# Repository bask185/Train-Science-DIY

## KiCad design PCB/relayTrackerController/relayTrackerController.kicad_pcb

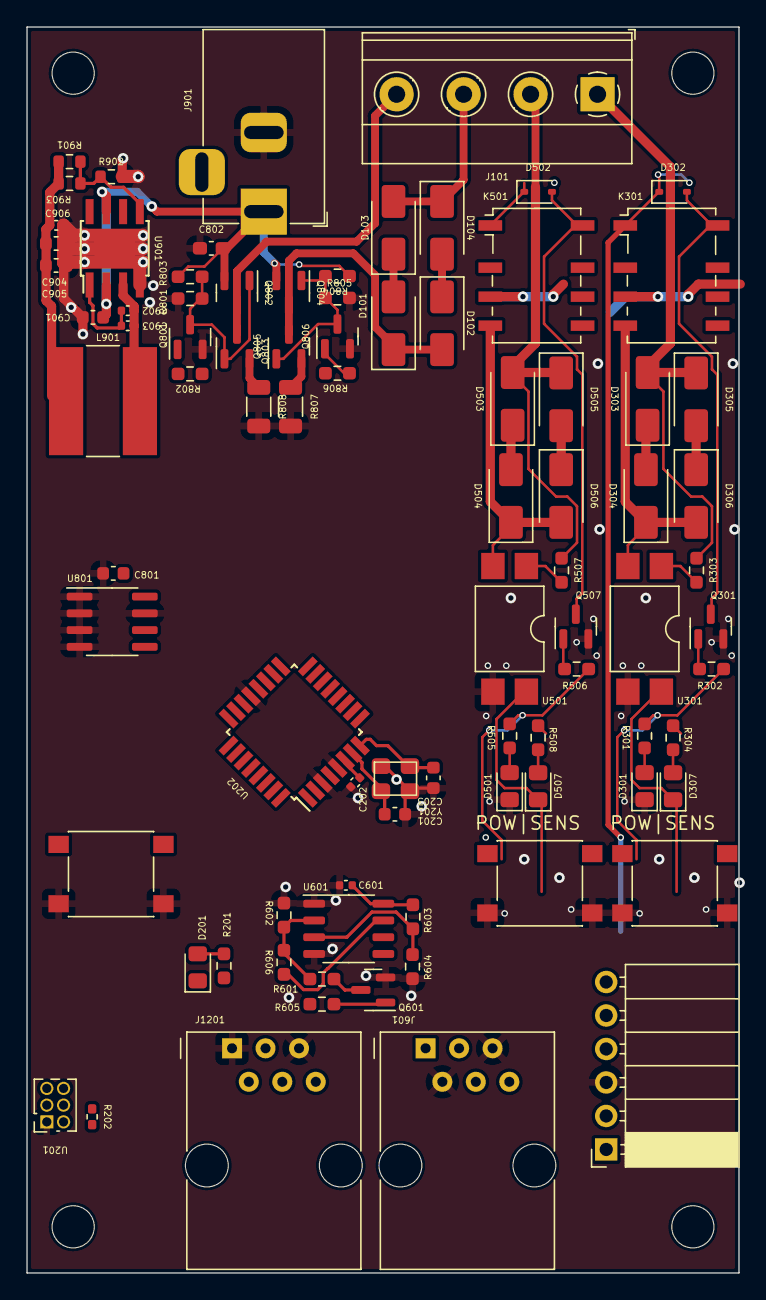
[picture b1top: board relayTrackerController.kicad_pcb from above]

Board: 2 copper layers, 54.0 x 94.5 mm, 86 parts (0 on the bottom side), 61 nets.

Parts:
C201, C203: 12pF; C_0603_1608Metric
C202, C601, C902, C906: 100nF; C_0402_1005Metric
C801: 100nF; C_0603_1608Metric
C802: 100nF; C_0603_1608Metric_Pad1.08x0.95mm_HandSolder
C901, C904, C905: 22uF; C_0603_1608Metric
C903: 22nF; C_0402_1005Metric
D101, D102, D103, D104, D303, D304, D305, D306, D503, D504, D505, D506: SS53; D_SMA
D201, D301, D307, D501, D507: LED; LED_0805_2012Metric_Pad1.15x1.40mm_HandSolder
D302, D502: 1N4148WS; D_SOD-323
J101: Screw_Terminal_01x04; TerminalBlock_Phoenix_MKDS-1,5-4-5.08_1x04_P5.08mm_Horizont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
J403: Conn_01x06_Socket; PinSocket_1x06_P2.54mm_Horizontal
J601, J1201: RJ12
J901: Jack-DC; BarrelJack_Horizontal
K301, K501: G6K-2F-Y-TR DC12; Relay_DPDT_Omron_G6K-2F-Y
L901: L; L_Bourns-SRN8040_8x8.15mm
Q301, Q507, Q601, Q801, Q806: NPN_TOR; SOT-23
Q802, Q804: P-channel; SOT-23
Q803, Q805: N-channel; SOT-23
R201: 6k2; R_0603_1608Metric_Pad0.98x0.95mm_HandSolder
R202: 10k; R_0402_1005Metric_Pad0.72x0.64mm_HandSolder
R301, R304, R505, R508: 3k3; R_0603_smalltext
R302, R506, R605, R802, R806: 1k; R_0603_smalltext
R303, R507: 47R; R_0603_smalltext
R601: 47k; R_0603_smalltext
R602: 150k; R_0603_smalltext
R603, R803, R804: 10k; R_0603_smalltext
R604: 22k; R_0603_smalltext
R606: 220k; R_0603_smalltext
R801, R805: 15k; R_0603_smalltext
R807, R808: 0R1; R_1206_3216Metric
R901: 220k; R_0603_1608Metric
R902: 20k; R_0603_1608Metric
R903: 150k; R_0603_1608Metric
SW201, SW301, SW501: SW_Push; tactile_SMD_6mm
U201: HEADER_3x2; PinSocket_2x03_P1.27mm_Vertical
U202: ATmega328-A; TQFP-32_7x7mm_P0.8mm
U301, U501: EL814; SMDIP-4_W9.53mm
U601: LM311; SOP-8_3.9x4.9mm_P1.27mm
U801: 24LC256; SOIC-8_3.9x4.9mm_P1.27mm
U901: MT2499A; TI_SO-PowerPAD-8
Y201: Crystal_GND2; crystal_arduino

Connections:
+5V: C202.1, C601.1, C801.2, C904.1, C905.1, C906.1, J403.5, J1201.6, L901.2, R201.1, R202.1, R304.1, R508.1, R603.1, R901.1, R903.2, U201.5, U202.4 (VCC), U202.6 (VCC), U202.18 (AVCC), U601.8 (V+), U801.8 (VCC)
/B2B/Rx: J403.1, U202.31 (PD1)
/B2B/Tx: J403.2, U202.30 (PD0)
/CPU/A: R802.1, U202.14 (PB2)
/CPU/B: R806.2, U201.3, U202.15 (PB3)
/CPU/CS: Q803.2 (S), Q805.2 (S), R807.1, R808.1, U202.23 (PC0)
/CPU/LED: D201.1 (K), U201.4, U202.17 (PB5)
/CPU/Lnet.Rx: R606.2, U202.12 (PB0), U601.7
/CPU/Lnet.Tx: R605.2, U202.13 (PB1)
/CPU/MISO: SW201.1, U201.6, U202.16 (PB4)
/CPU/SCL: U202.28 (PC5), U801.6 (SCL)
/CPU/SDA: U202.27 (PC4), U801.5 (SDA)
/CPU/X1: C201.2, U202.7 (XTAL1/PB6), Y201.1
/CPU/X2: C203.2, U202.8 (XTAL2/PB7), Y201.3
/CPU/brake: J1201.3, U202.25 (PC2)
/CPU/dir: J1201.4, U202.24 (PC1)
/CPU/relay1.add: SW301.1, U202.2 (PD4)
/CPU/relay1.relay: R301.1, R302.1, U202.1 (PD3)
/CPU/relay1.sensor: D307.1 (K), U202.32 (PD2), U301.4
/CPU/relay2.add: SW501.1, U202.11 (PD7)
/CPU/relay2.relay: R505.1, R506.1, U202.10 (PD6)
/CPU/relay2.sensor: D507.1 (K), U202.9 (PD5), U501.4
/CPU/reset: R202.2, U201.2, U202.29 (~RESET/PC6)
/CPU/throttle: J1201.2, U202.26 (PC3)
/PWM/OUT_A: J101.4, Q802.3 (D), Q803.3 (D)
/PWM/OUT_B: D101.1 (K), D102.2 (A), J403.6, K301.3, K501.3, Q804.3 (D), Q805.3 (D)
/relay1/TRACK: D303.2 (A), D305.1 (K), J101.1, R303.1
/relay2/TRACK: D503.2 (A), D505.1 (K), J101.2, R507.1
GND: C201.1, C202.2, C203.1, C601.2, C801.1, C802.1, C901.2, C904.2, C905.2, C906.2, D301.1 (K), D501.1 (K), J403.3, J601.2, J601.5, J901.2, J1201.1, J1201.5, Q301.2 (E), Q507.2 (E), Q601.2 (E), Q801.2 (E), Q806.2 (E), R602.2, R604.1, R801.1, R805.2, R807.2, R808.2, R902.2, SW201.2, SW301.2, SW501.2, U201.1, U202.3 (GND), U202.5 (GND), U202.21 (GND), U301.3, U501.3, U601.1 (GND), U601.4 (V-), U801.1 (A0), U801.2 (A1), U801.3 (A2), U801.4 (GND), U801.7 (WP), U901.4 (GND), U901.9 (GND), Y201.2 (GND), Y201.4 (GND)
unnamed: D101.2 (A), D103.1 (K)
unnamed: D102.1 (K), D104.2 (A)
unnamed: D103.2 (A), D104.1 (K), J101.3
unnamed: D201.2 (A), R201.2
unnamed: D301.2 (A), R301.2
unnamed: D302.2 (A), K301.8, Q301.3 (C)
unnamed: D303.1 (K), D304.2 (A)
unnamed: D304.1 (K), D306.2 (A), K301.4, U301.2
unnamed: D305.2 (A), D306.1 (K)
unnamed: D307.2 (A), R304.2
unnamed: D501.2 (A), R505.2
unnamed: D502.2 (A), K501.8, Q507.3 (C)
unnamed: D503.1 (K), D504.2 (A)
unnamed: D504.1 (K), D506.2 (A), K501.4, U501.2
unnamed: D505.2 (A), D506.1 (K)
unnamed: D507.2 (A), R508.2
unnamed: Q301.1 (B), R302.2
unnamed: Q507.1 (B), R506.2
unnamed: Q601.1 (B), R605.1
unnamed: J601.3, J601.4, Q601.3 (C), R601.1
unnamed: Q801.1 (B), R802.2
unnamed: Q801.3 (C), Q802.1 (G), Q803.1 (G), R801.2, R803.2
unnamed: Q804.1 (G), Q805.1 (G), Q806.3 (C), R804.2, R805.1
unnamed: Q806.1 (B), R806.1
unnamed: R303.2, U301.1
unnamed: R507.2, U501.1
unnamed: R601.2, R602.1, R606.1, U601.2 (+)
unnamed: R603.2, R604.2, U601.3 (-)
unnamed: C902.1, C903.1, U901.1 (BS)
unnamed: R901.2, R902.1, R903.1, U901.5 (FB)
unnamed: C902.2, C903.2, L901.1, U901.3 (SW)
VCC: C802.2, C901.1, D302.1 (K), D502.1 (K), J403.4, J601.1, J601.6, J901.1, K301.1, K501.1, Q802.2 (S), Q804.2 (S), R803.1, R804.1, U901.2 (Vin), U901.7 (EN)

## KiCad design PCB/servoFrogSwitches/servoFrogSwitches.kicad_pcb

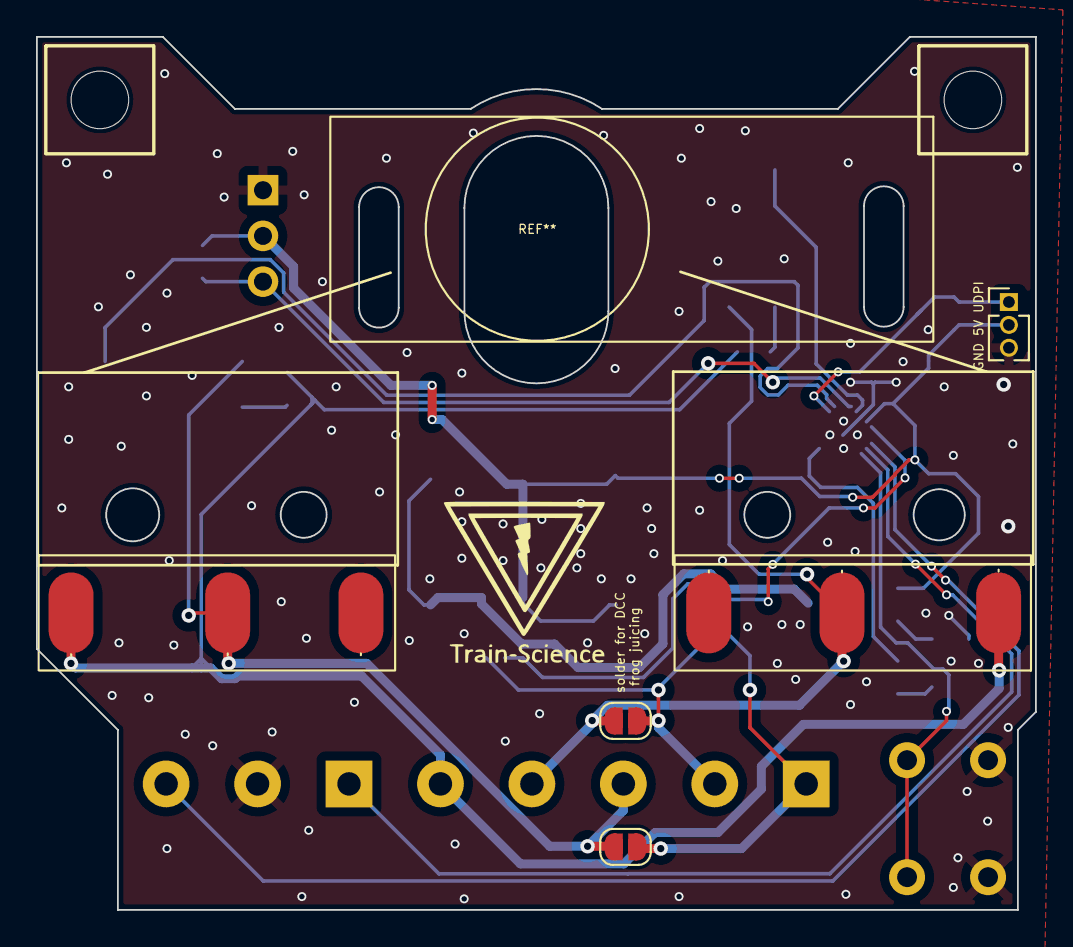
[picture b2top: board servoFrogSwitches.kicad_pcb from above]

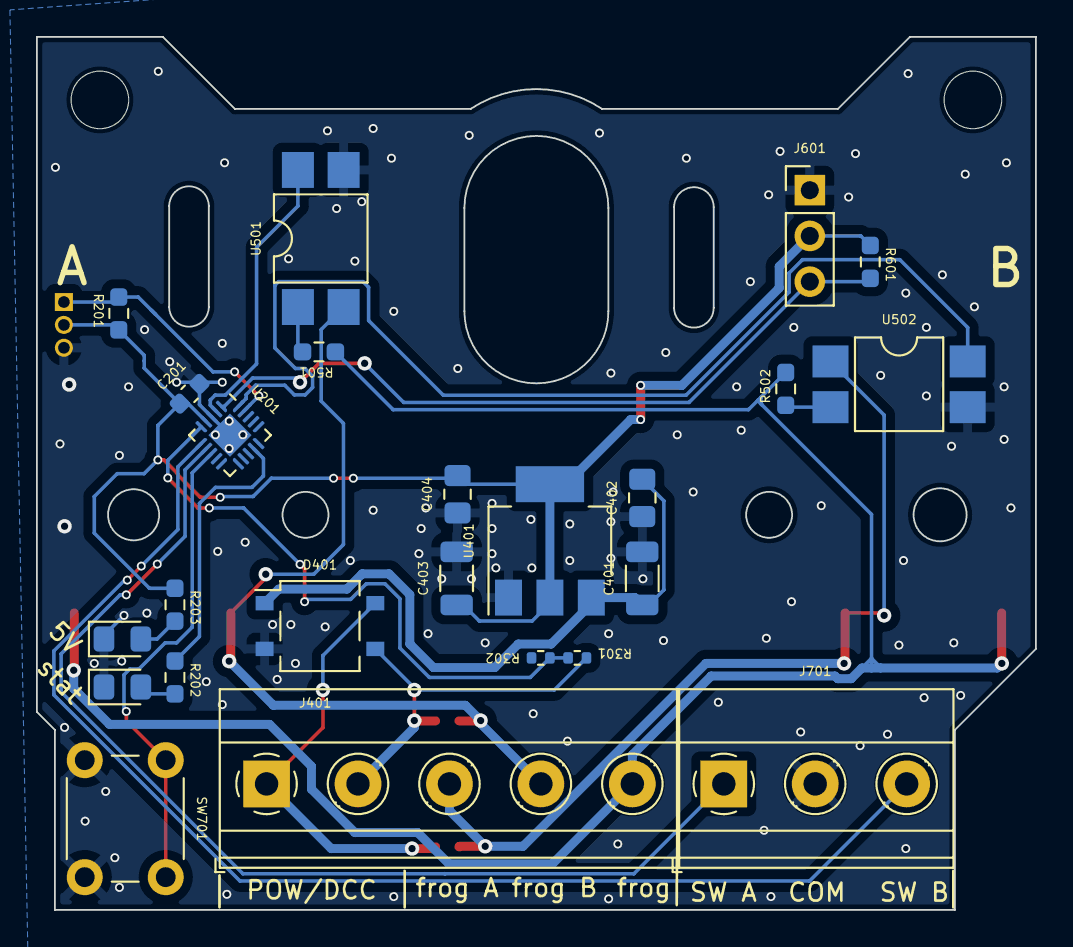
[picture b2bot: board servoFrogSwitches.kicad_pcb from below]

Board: 2 copper layers, 55.5 x 48.5 mm, 29 parts (24 on the bottom side), 21 nets.

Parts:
C201: 100nF; C_0603_1608Metric
C401: 47uF; C_1206_3216Metric
C402, C404: 100nF; C_0805_2012Metric_Pad1.18x1.45mm_HandSolder
C403: 100uF; C_1206_3216Metric
D201, D202: LED; LED_0805_2012Metric_Pad1.15x1.40mm_HandSolder
D401: MB10S; TO-269AA
J201: Conn_01x03_Pin; PinHeader_1x03_P1.27mm_Vertical
J401: Screw_Terminal_01x05; TerminalBlock_Phoenix_MKDS-1,5-5-5.08_1x05_P5.08mm_Horizont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
J601: Conn_01x03; PinHeader_1x03_P2.54mm_Vertical
J701: Screw_Terminal_01x03; TerminalBlock_Phoenix_MKDS-1,5-3-5.08_1x03_P5.08mm_Horizont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
JP401, JP402: SolderJumper_2_Open; SolderJumper-2_P1.3mm_Open_RoundedPad1.0x1.5mm
R201, R601: 10k; R_0603_smalltext
R202, R203: 680R; R_0603_smalltext
R301: 26k; R_0402_1005Metric
R302: 10k; R_0402_1005Metric
R501, R502: 1k5; R_0603_smalltext
SW501, SW502: SW_SPDT; microswitch
SW701: 6mm_tactile; SW_PUSH_6mm
U201: ATtiny1616-M; VQFN-20-1EP_3x3mm_P0.4mm_EP1.7x1.7mm
U401: AMS1117-5.0; SOT-223-3_TabPin2
U501, U502: EL814; SMDIP-4_W7.62mm

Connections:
+5V: C201.1, C403.1, C404.2, J201.2, J601.2, R201.1, R203.1, R601.1, U201.4 (VCC), U401.2 (VO)
/DCC/DCC_A: D401.3, J401.2, JP401.2 (B), R301.1
/DCC/DCC_TTL: R301.2, R302.1, U201.5 (PA4)
/attiny/LIM_A: U201.20 (PA1), U502.4
/attiny/LIM_B: U201.2 (PA3), U501.4
/attiny/UPDI: J201.1, R201.2, U201.19 (~RESET/PA0)
/attiny/control_A: J701.3, U201.6 (PA5)
/attiny/control_B: J701.1, U201.7 (PA6)
/attiny/finetune: SW701.1 (A), U201.8 (PA7)
/attiny/servo: J601.3, R601.2, U201.1 (PA2)
/limitSwitches/DCC_A: J401.4, JP401.1 (A), SW501.3 (C), U501.2
/limitSwitches/DCC_B: J401.3, JP402.1 (A), SW502.3 (C), U502.1
/limitSwitches/FROG: J401.5, R501.1, R502.2, SW501.2 (B), SW502.2 (B)
/power/DCC_B: D401.4, J401.1, JP402.2 (B)
GND: C201.2, C401.2, C402.1, C403.2, C404.1, D201.1 (K), D202.1 (K), D401.2 (-), J201.3, J601.1, J701.2, SW701.2 (B), U201.3 (GND), U201.21 (GND), U401.1 (GND), U501.3, U502.3
unnamed: D201.2 (A), R202.2
unnamed: D202.2 (A), R203.2
unnamed: R501.2, U501.1
unnamed: R502.1, U502.2
unnamed: R202.1, U201.14 (PB0)
VCC: C401.1, C402.2, D401.1 (+), U401.3 (VI)

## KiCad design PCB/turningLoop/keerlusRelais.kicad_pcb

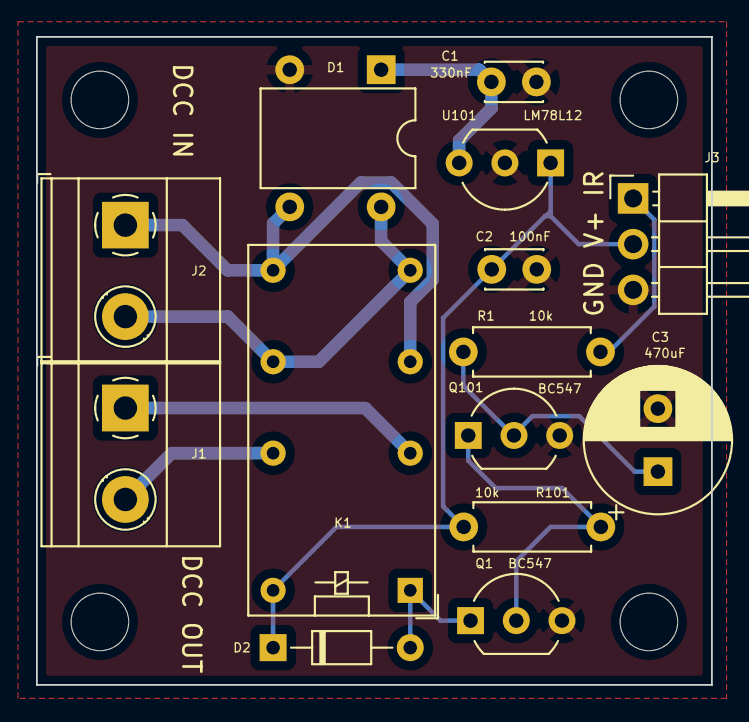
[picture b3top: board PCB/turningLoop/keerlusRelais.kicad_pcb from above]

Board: 2 copper layers, 37.5 x 36.0 mm, 14 parts (0 on the bottom side), 11 nets.

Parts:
C1: 330nF; C_Disc_D3.0mm_W2.0mm_P2.50mm
C2: 100nF; C_Disc_D3.0mm_W2.0mm_P2.50mm
C3: 470uF; CP_Radial_D8.0mm_P3.50mm
D1: D_Bridge_+-AA; Diode_Bridge_DIP-4_W7.62mm_P5.08mm
D2: D; D_DO-34_SOD68_P7.62mm_Horizontal
J1: DCC_out; TerminalBlock_Phoenix_MKDS-1,5-2-5.08_1x02_P5.08mm_Horizont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
J2: DCC_IN; TerminalBlock_Phoenix_MKDS-1,5-2-5.08_1x02_P5.08mm_Horizont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
J3: Conn_01x03_Male; PinHeader_1x03_P2.54mm_Horizontal
K1: G5V-2; Relay_DPDT_Omron_G5V-2
Q1, Q101: BC547; TO-92_Inline_Wide
R1, R101: 10k; R_Axial_DIN0207_L6.3mm_D2.5mm_P7.62mm_Horizontal
U101: LM78L12; TO-92_Inline_Wide

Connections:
+12V: C2.1, D2.1 (K), J3.2, K1.16, R101.2, U101.1 (VO)
/DCC_A_IN: D1.3, J2.1, K1.6, K1.9
/DCC_A_OUT: J1.1, K1.4
/DCC_B_IN: D1.4, J2.2, K1.8, K1.11
/DCC_B_OUT: J1.2, K1.13
GND: C1.2, C2.2, C3.2, D1.2 (-), J3.3, Q1.3 (E), Q101.3 (E), U101.2 (GND)
unnamed: D2.2 (A), K1.1, Q1.1 (C)
unnamed: J3.1, R1.2
unnamed: Q1.2 (B), Q101.1 (C), R101.1
unnamed: C3.1, Q101.2 (B), R1.1
VCC: C1.1, D1.1 (+), U101.3 (VI)

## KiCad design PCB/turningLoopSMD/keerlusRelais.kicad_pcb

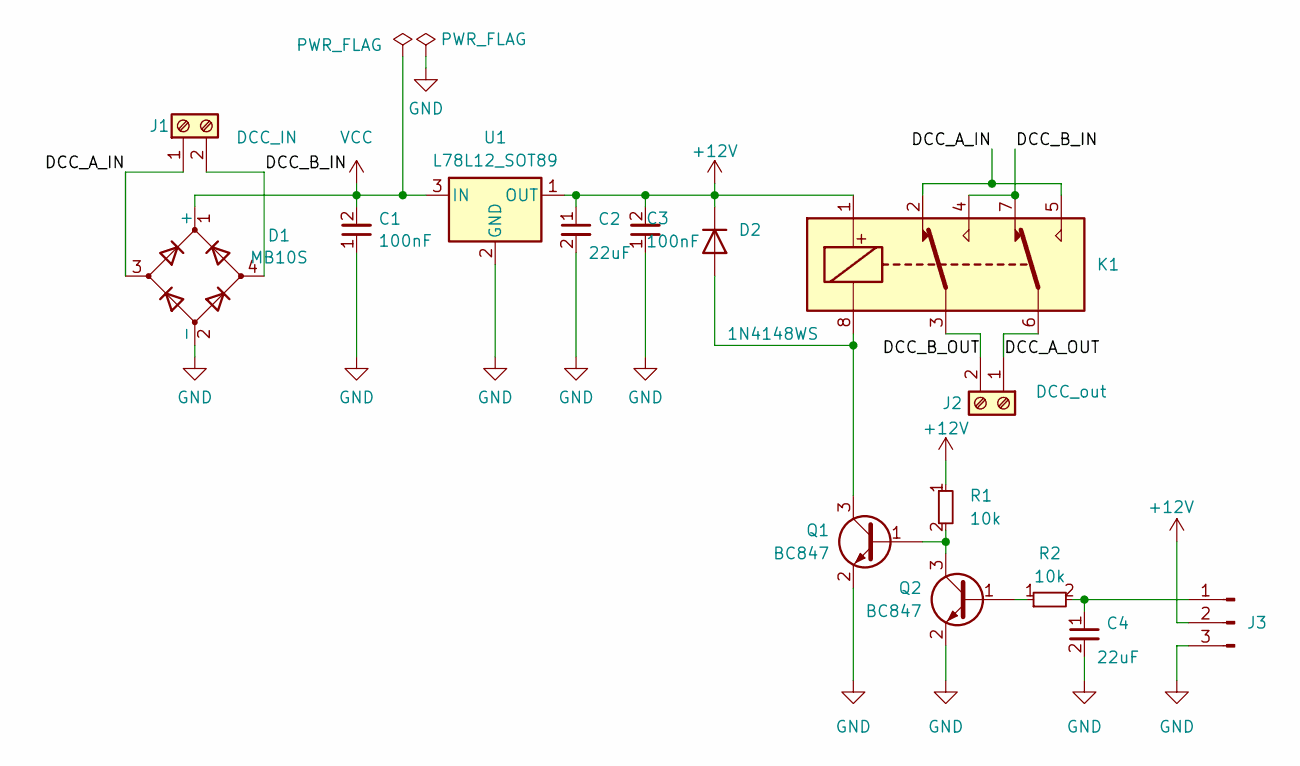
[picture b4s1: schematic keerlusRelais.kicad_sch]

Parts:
C1, C3: 100nF; C_0603_1608Metric; JLCPCB Part# C14663
C2, C4: 22uF; C_1206_3216Metric; JLCPCB Part# C12891
D1: MB10S; MB10s; JLCPCB Part# C2488
D2: 1N4148WS; D_SOD-323; JLCPCB Part# C2128
J1: DCC_IN; TerminalBlock_Phoenix_MKDS-1,5-2-5.08_1x02_P5.08mm_Horizont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
J2: DCC_out; TerminalBlock_Phoenix_MKDS-1,5-2-5.08_1x02_P5.08mm_Horizont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
J3: Conn_01x03_Male; PinHeader_1x03_P2.54mm_Horizontal
K1: G6K-2F-Y-TR DC5; Relay_DPDT_Omron_G6K-2F-Y; JLCPCB Part# C397192
Q1, Q2: BC847; SOT-23; JLCPCB Part# C181140
R1, R2: 10k; R_0603_smalltext; JLCPCB Part# C25804
U1: L78L12_SOT89; SOT-89-3; JLCPCB Part# C75501

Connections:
+12V: C2.1, C3.2, D2.1 (K), J3.2, K1.1, R1.1, U1.1 (OUT)
/DCC_A_IN: D1.3, J1.1, K1.2, K1.5
/DCC_A_OUT: J2.1, K1.6
/DCC_B_IN: D1.4, J1.2, K1.4, K1.7
/DCC_B_OUT: J2.2, K1.3
GND: C1.1, C2.2, C3.1, C4.2, D1.2 (-), J3.3, Q1.2 (E), Q2.2 (E), U1.2 (GND)
unnamed: D2.2 (A), K1.8, Q1.3 (C)
unnamed: C4.1, J3.1, R2.2
unnamed: Q1.1 (B), Q2.3 (C), R1.2
unnamed: Q2.1 (B), R2.1
VCC: C1.2, D1.1 (+), U1.3 (IN)

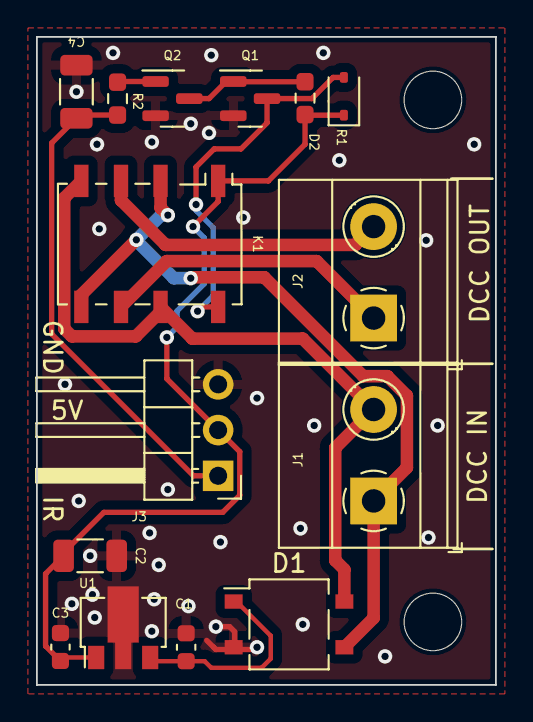
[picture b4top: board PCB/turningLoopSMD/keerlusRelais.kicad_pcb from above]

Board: 2 copper layers, 25.5 x 36.0 mm, 15 parts (0 on the bottom side), 11 nets.

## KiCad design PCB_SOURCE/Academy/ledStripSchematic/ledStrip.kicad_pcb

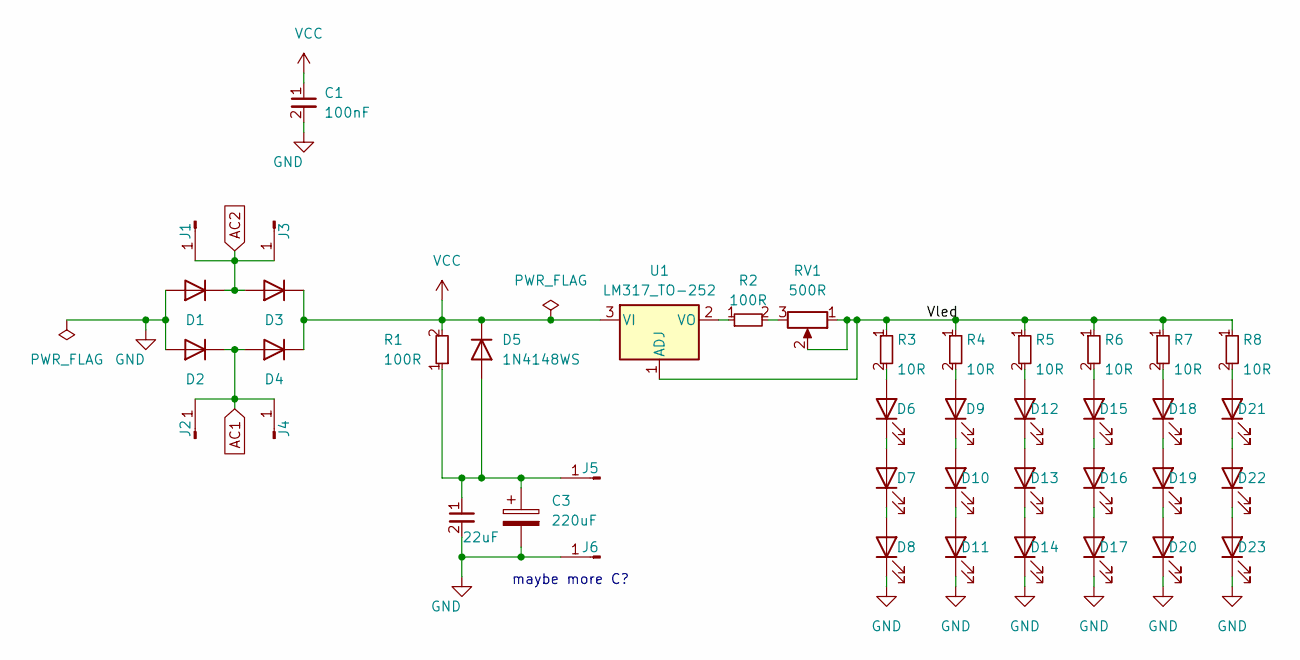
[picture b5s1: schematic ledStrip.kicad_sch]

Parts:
C1: 100nF; C_0603_1608Metric; JLCPCB Part# C14663
C2: 22uF; C_1206_3216Metric; JLCPCB Part# C12891
C3: 220uF; C_Elec_8x10.2; JLCPCB Part# C136294
D1, D2, D3, D4, D5: 1N4148WS; D_SOD-323; JLCPCB Part# C2128
D6, D7, D8, D9, D10, D11, D12, D13, D14, D15, D16, D17, D18, D19, D20, D21, D22, D23: LED; LED_0805_2012Metric; JLCPCB Part# C965820
J1, J2, J3, J4, J5, J6: Conn_01x01_Pin; 01_solderpad_2.54
R1: 100R; R_0805_handsolder-smalltext; JLCPCB Part# C17408
R2: 100R; R_0603_smalltext; JLCPCB Part# C22775
R3, R4, R5, R6, R7, R8: 10R; R_0603_smalltext; JLCPCB Part# C22859
RV1: 500R; Potentiometer_Bourns_TC33X_Vertical; JLCPCB Part# C720649
U1: LM317_TO-252; TO-252-2; JLCPCB Part# C75510

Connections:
/Vled: R3.1, R4.1, R5.1, R6.1, R7.1, R8.1, RV1.1, RV1.2, U1.1 (ADJ)
AC1: D2.1 (K), D4.2 (A), J2.1, J4.1
AC2: D1.1 (K), D3.2 (A), J1.1, J3.1
GND: C1.2, C2.2, C3.2, D1.2 (A), D2.2 (A), D8.1 (K), D11.1 (K), D14.1 (K), D17.1 (K), D20.1 (K), D23.1 (K), J6.1
unnamed: C2.1, C3.1, D5.2 (A), J5.1, R1.1
unnamed: D6.2 (A), R3.2
unnamed: D6.1 (K), D7.2 (A)
unnamed: D7.1 (K), D8.2 (A)
unnamed: D9.2 (A), R4.2
unnamed: D9.1 (K), D10.2 (A)
unnamed: D10.1 (K), D11.2 (A)
unnamed: D12.2 (A), R5.2
unnamed: D12.1 (K), D13.2 (A)
unnamed: D13.1 (K), D14.2 (A)
unnamed: D15.2 (A), R6.2
unnamed: D15.1 (K), D16.2 (A)
unnamed: D16.1 (K), D17.2 (A)
unnamed: D18.2 (A), R7.2
unnamed: D18.1 (K), D19.2 (A)
unnamed: D19.1 (K), D20.2 (A)
unnamed: D21.2 (A), R8.2
unnamed: D21.1 (K), D22.2 (A)
unnamed: D22.1 (K), D23.2 (A)
unnamed: R2.2, RV1.3
unnamed: R2.1, U1.2 (VO)
VCC: C1.1, D3.1 (K), D4.1 (K), D5.1 (K), R1.2, U1.3 (VI)

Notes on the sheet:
maybe more C?

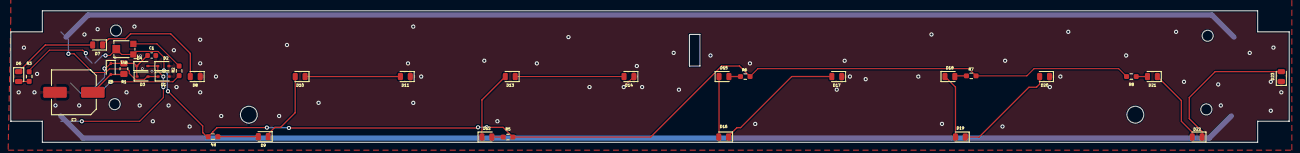
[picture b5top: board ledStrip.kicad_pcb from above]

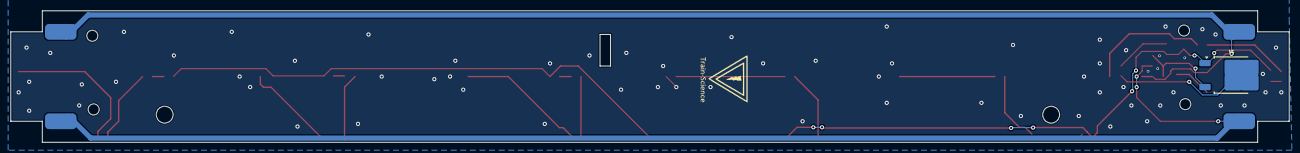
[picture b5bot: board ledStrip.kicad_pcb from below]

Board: 2 copper layers, 243.0 x 25.0 mm, 39 parts (5 on the bottom side), 26 nets.

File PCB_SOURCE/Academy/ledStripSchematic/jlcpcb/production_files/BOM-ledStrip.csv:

Comment,Designator,Footprint,LCSC
220uF,C3,C_Elec_8x10.2,C136294
100nF,C1,C_0603_1608Metric,C14663
100R,R1,R_0805_handsolder-smalltext,C17408
1N4148WS,"D1,D2,D3,D4,D5",D_SOD-323,C2128
100R,R2,R_0603_smalltext,C22775
10R,"R3,R4,R5,R6,R7,R8",R_0603_smalltext,C22859
500R,RV1,Potentiometer_Bourns_TC33X_Vertical,C720649
LED,"D10,D11,D12,D13,D14,D15,D16,D17,D18,D19,D20,D21,D22,D23,D6,D7,D8,D9",LED_0805_2012Metric,C965820

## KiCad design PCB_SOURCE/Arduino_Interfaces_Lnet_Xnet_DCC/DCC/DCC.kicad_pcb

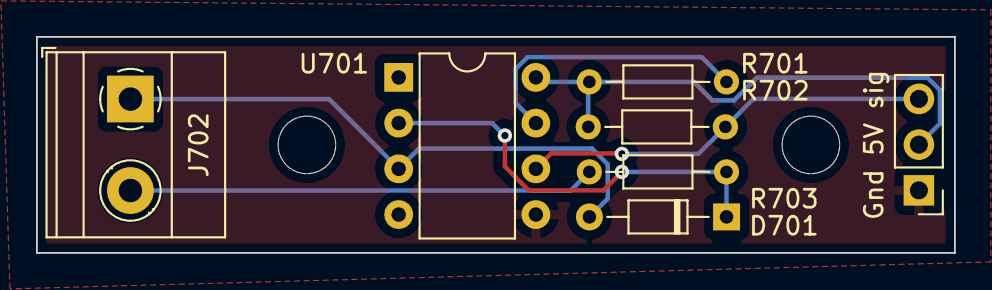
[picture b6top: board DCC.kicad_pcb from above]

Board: 2 copper layers, 51.0 x 12.0 mm, 7 parts (0 on the bottom side), 7 nets.

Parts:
D701: D; D_DO-34_SOD68_P7.62mm_Horizontal
J701: Conn_01x03_Male; PinHeader_1x03_P2.54mm_Vertical
J702: Screw_Terminal_01x02; TerminalBlock_Phoenix_MKDS-1,5-2-5.08_1x02_P5.08mm_Horizont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
R701, R702: 10k; R_Axial_DIN0204_L3.6mm_D1.6mm_P7.62mm_Horizontal
R703: 1k; R_Axial_DIN0204_L3.6mm_D1.6mm_P7.62mm_Horizontal
U701: 6N137; DIP-8_W7.62mm

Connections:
+5V: J701.2, R701.1, R702.1, U701.8 (VCC)
DCC-A: J702.2, R703.1
DCC-B: D701.2 (A), J702.1, U701.3 (C)
DCC_IN: J701.3, R702.2, U701.6 (VO)
GND: J701.1, U701.5 (GND)
unnamed: D701.1 (K), R703.2, U701.2 (A)
unnamed: R701.2, U701.7 (EN)

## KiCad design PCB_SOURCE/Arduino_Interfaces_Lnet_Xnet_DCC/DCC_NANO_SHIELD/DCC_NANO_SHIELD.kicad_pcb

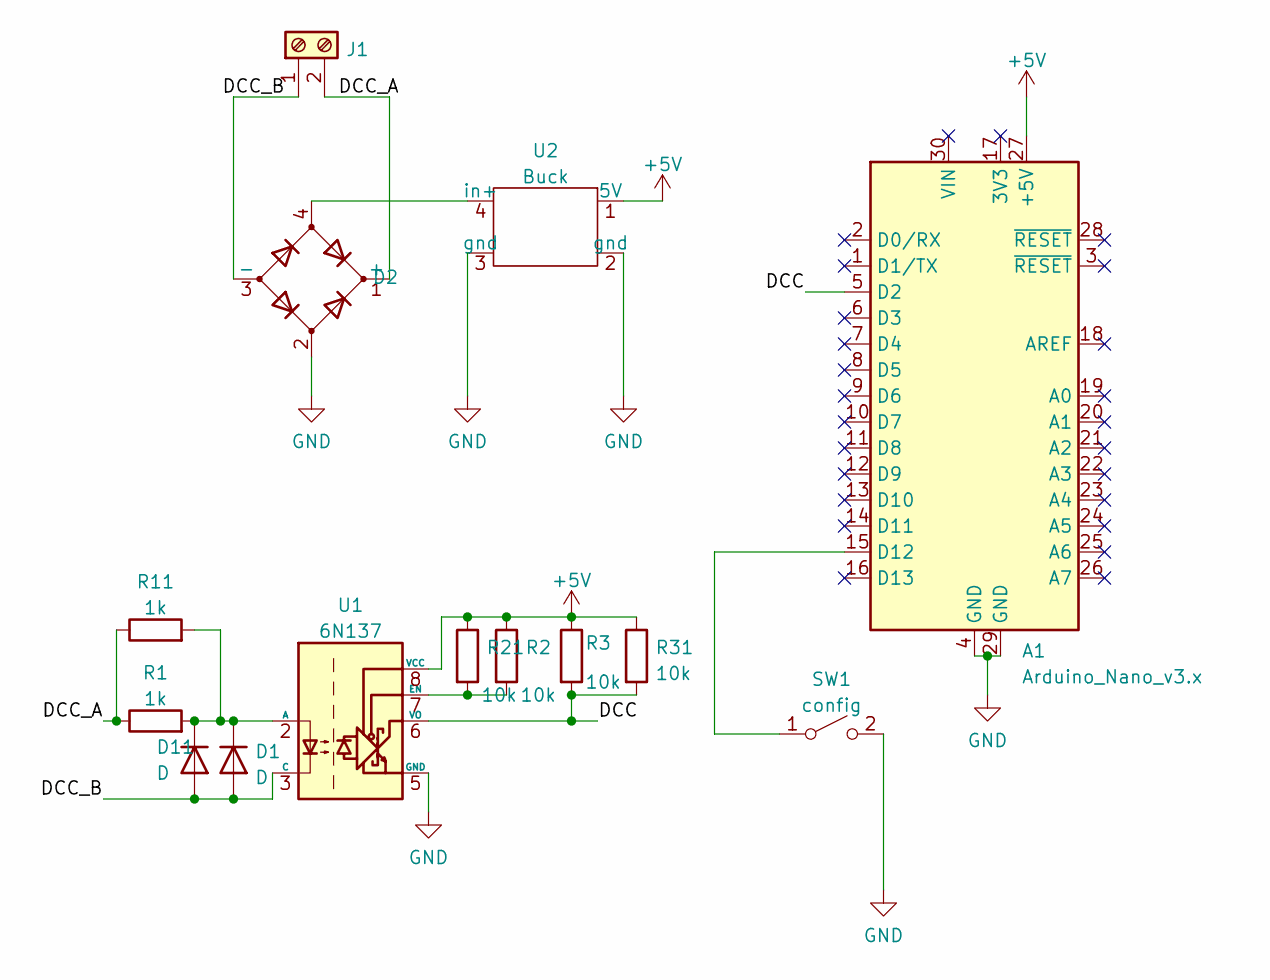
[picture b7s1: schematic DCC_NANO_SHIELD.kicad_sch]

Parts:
A1: Arduino_Nano_v3.x; Arduino_Nano
D1: D; D_DO-34_SOD68_P7.62mm_Horizontal
D2: D_Bridge_+A-A; Diode_Bridge_Round_D9.0mm
D11: D; D_1206_3216Metric_Pad1.42x1.75mm_HandSolder
J1: Screw_Terminal_01x02; TerminalBlock_Phoenix_MKDS-1,5-2-5.08_1x02_P5.08mm_Horizont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
R1: 1k; R_Axial_DIN0204_L3.6mm_D1.6mm_P7.62mm_Horizontal
R2, R3: 10k; R_Axial_DIN0204_L3.6mm_D1.6mm_P7.62mm_Horizontal
R11: 1k; R_0805_2012Metric_Pad1.20x1.40mm_HandSolder
R21, R31: 10k; R_0805_2012Metric_Pad1.20x1.40mm_HandSolder
SW1: config; SW_PUSH_6mm
U1: 6N137; DIP-8_W7.62mm
U2: Buck

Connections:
+5V: A1.27 (+5V), R2.1, R3.1, R21.1, R31.1, U1.8 (VCC), U2.1 (5V)
/DCC: A1.5 (D2), R3.2, R31.2, U1.6 (VO)
/DCC_A: D2.1 (+), J1.2, R1.1, R11.1
/DCC_B: D1.2 (A), D2.3 (-), D11.2 (A), J1.1, U1.3 (C)
GND: A1.4 (GND), A1.29 (GND), D2.2, SW1.2 (B), U1.5 (GND), U2.2 (gnd), U2.3 (gnd)
unnamed: A1.15 (D12), SW1.1 (A)
unnamed: D1.1 (K), D11.1 (K), R1.2, R11.2, U1.2 (A)
unnamed: D2.4, U2.4 (in+)
unnamed: R2.2, R21.2, U1.7 (EN)

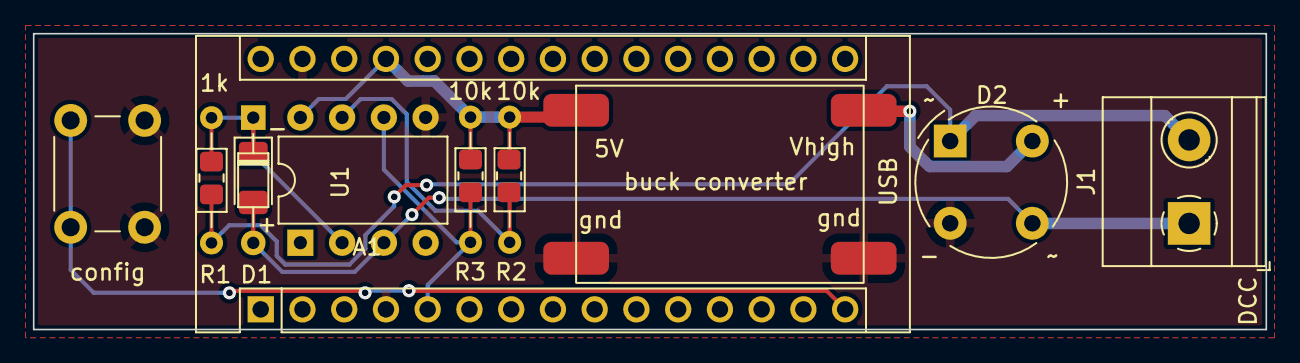
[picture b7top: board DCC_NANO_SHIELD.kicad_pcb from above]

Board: 2 copper layers, 75.0 x 18.0 mm, 14 parts (0 on the bottom side), 9 nets.

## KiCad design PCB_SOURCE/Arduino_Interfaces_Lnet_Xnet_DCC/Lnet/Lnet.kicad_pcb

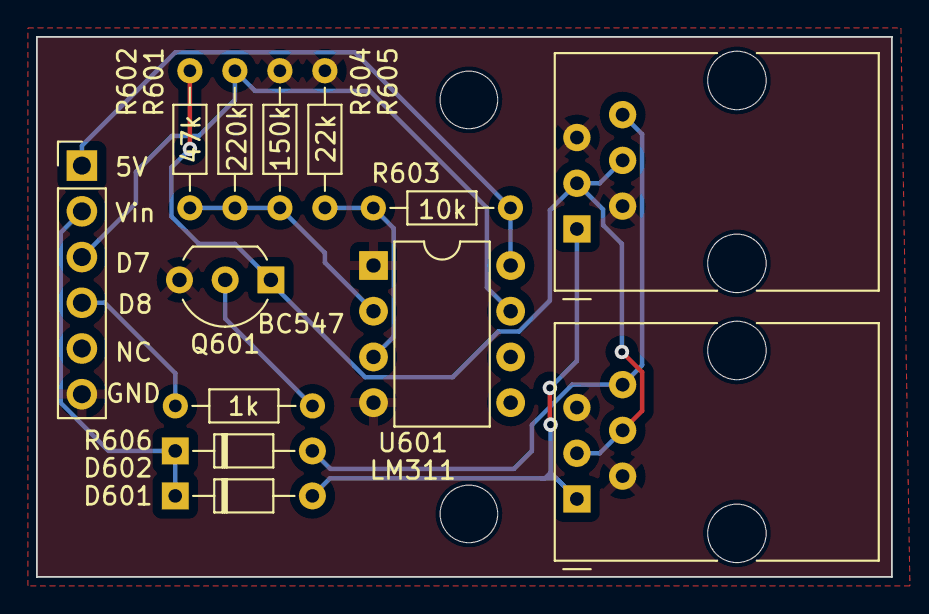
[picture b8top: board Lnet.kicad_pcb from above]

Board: 2 copper layers, 47.5 x 30.0 mm, 13 parts (0 on the bottom side), 11 nets.

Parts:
D601, D602: D; D_DO-34_SOD68_P7.62mm_Horizontal
J601, J602: RJ12; RJ12_Amphenol_54601
J603: Conn_01x06_Male; PinHeader_1x06_P2.54mm_Vertical
Q601: BC547; TO-92_Inline_Wide
R601: 220k; R_Axial_DIN0204_L3.6mm_D1.6mm_P7.62mm_Horizontal
R602: 47k; R_Axial_DIN0204_L3.6mm_D1.6mm_P7.62mm_Horizontal
R603: 10k; R_Axial_DIN0204_L3.6mm_D1.6mm_P7.62mm_Horizontal
R604: 150k; R_Axial_DIN0204_L3.6mm_D1.6mm_P7.62mm_Horizontal
R605: 22k; R_Axial_DIN0204_L3.6mm_D1.6mm_P7.62mm_Horizontal
R606: 1k; R_Axial_DIN0204_L3.6mm_D1.6mm_P7.62mm_Horizontal
U601: LM311; DIP-8_W7.62mm

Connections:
+5V: J603.1, R603.2, U601.8 (V+)
+12V: D601.1 (K), D602.1 (K), J603.2
GND: J601.2, J601.5, J602.2, J602.5, J603.6, Q601.3 (E), R604.1, R605.1, U601.1 (GND), U601.4 (V-)
Lnet_Rx: J603.3, R601.2, U601.7
Lnet_Tx: J603.4, R606.2
unnamed: J601.3, J601.4, J602.3, J602.4, Q601.1 (C), R602.2
unnamed: R601.1, R602.1, R604.2, U601.2 (+)
unnamed: R603.1, R605.2, U601.3 (-)
unnamed: Q601.2 (B), R606.1
railsyncA: D602.2 (A), J601.6, J602.6
railsyncB: D601.2 (A), J601.1, J602.1
